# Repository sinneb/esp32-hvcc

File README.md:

# ESP32-DevKitC & hvcc

This repo demonstrates a single file solution for running [hvcc](https://github.com/enzienaudio/hvcc) sources on the [ESP32-devkitc](https://docs.espressif.com/projects/esp-idf/en/latest/hw-reference/get-started-devkitc.html), inspired by the [Faust ESP32 architecture example](https://faust.grame.fr/doc/tutorials/#dsp-on-the-esp32-with-faust). The hvcc compiler leverages the use of (a subset of) puredata operators on the cheap and fast esp32 uprocessor. The ESP32-devkitc combined with one PCM5102 CODEC, one WM8731 CODEC and an 8 port MCP3208 ADC provides a complete and available audio development platform with a very reasonable pricetag. UI provided via 4 buttons, 4 potentiometers and 4 leds.

# Goal

The goal of this development is to realise a generic eurorack module that is based on the ESP32 and programmable via puredata. Each cheap module consists of four control voltage inputs and four audio / cv outputs (all io -5v -> +5v and fully eurorack compatible). All parts are easily obtainable and all software and hardware is open source, so ordering your own set of PCB's is also possible

# Status
15-nov-2020: Replaced one of the PCM5102 with a WM8731 to have audio stereo line in over i2s

25-oct-2020: PCB design ready, gerbers generated and boards ordered.

18-oct-2020: Code cleanup and PCB design ongoing. Current schematic tested and working!

# Installation

- Install Espressif IoT Development Framework 4.1, the official development framework for ESP32.
- Install the hvcc compiler
- Clone this repo

# Hardware setup

Check the Kicad schematics in the schematics folder

# Usage

- Create your puredata patch, using the [supported objects](supportedobjects.md) only. Use `tabread` with a $0-array instead of the `table` object, seems to work better.
- Issue a Issue a `python2.7 hvcc.py input.pd -o ./heavy/` to generate the source files, where input.pd is your puredata patch
- MAC: compile using hvcc and libs and copy to project subdir: `python2.7 hvcc.py esp32_2.pd -p ./Hoclib/ ./Josephlarralde/ ./ParkinsonHashizume/ ./MikeMorenoAudio/ ./Heavylib -o ./heavy/ ; cp ./heavy/c/Heavy_heavy.* ~/Documents/GitHub/esp32-hvcc/main/heavy/`
- WIN: compile and copy: `c:\Python27\python.exe` rest as above, then a `copy /Y heavy\c\Heavy_* c:\Users\Arthur\Github\esp32-hvcc\main\heavy`
- Add all heavy c and cpp sources to /main/CMakeLists.txt (only when adding new objects)
- Run `idf.py -p /dev/tty.SLAB_USBtoUART flash monitor` to compile, upload and monitor the esp32 binary
- MAC: `idf.py -p /dev/cu.usbserial-1A14301 -b 921600 flash monitor`
- WIN: `idf.py -p COM4 -b 921600 flash monitor`
- Enjoy your pd patch!

# Performance

A large and nice sounding puredata patch from "manwithfeathers" on rebeltech.org named ["Fascination IV"](https://www.rebeltech.org/patch-library/patch/Fascination_IV) yields about 60% performance of the ESP32 which looks like a very nice performance / cost ratio!

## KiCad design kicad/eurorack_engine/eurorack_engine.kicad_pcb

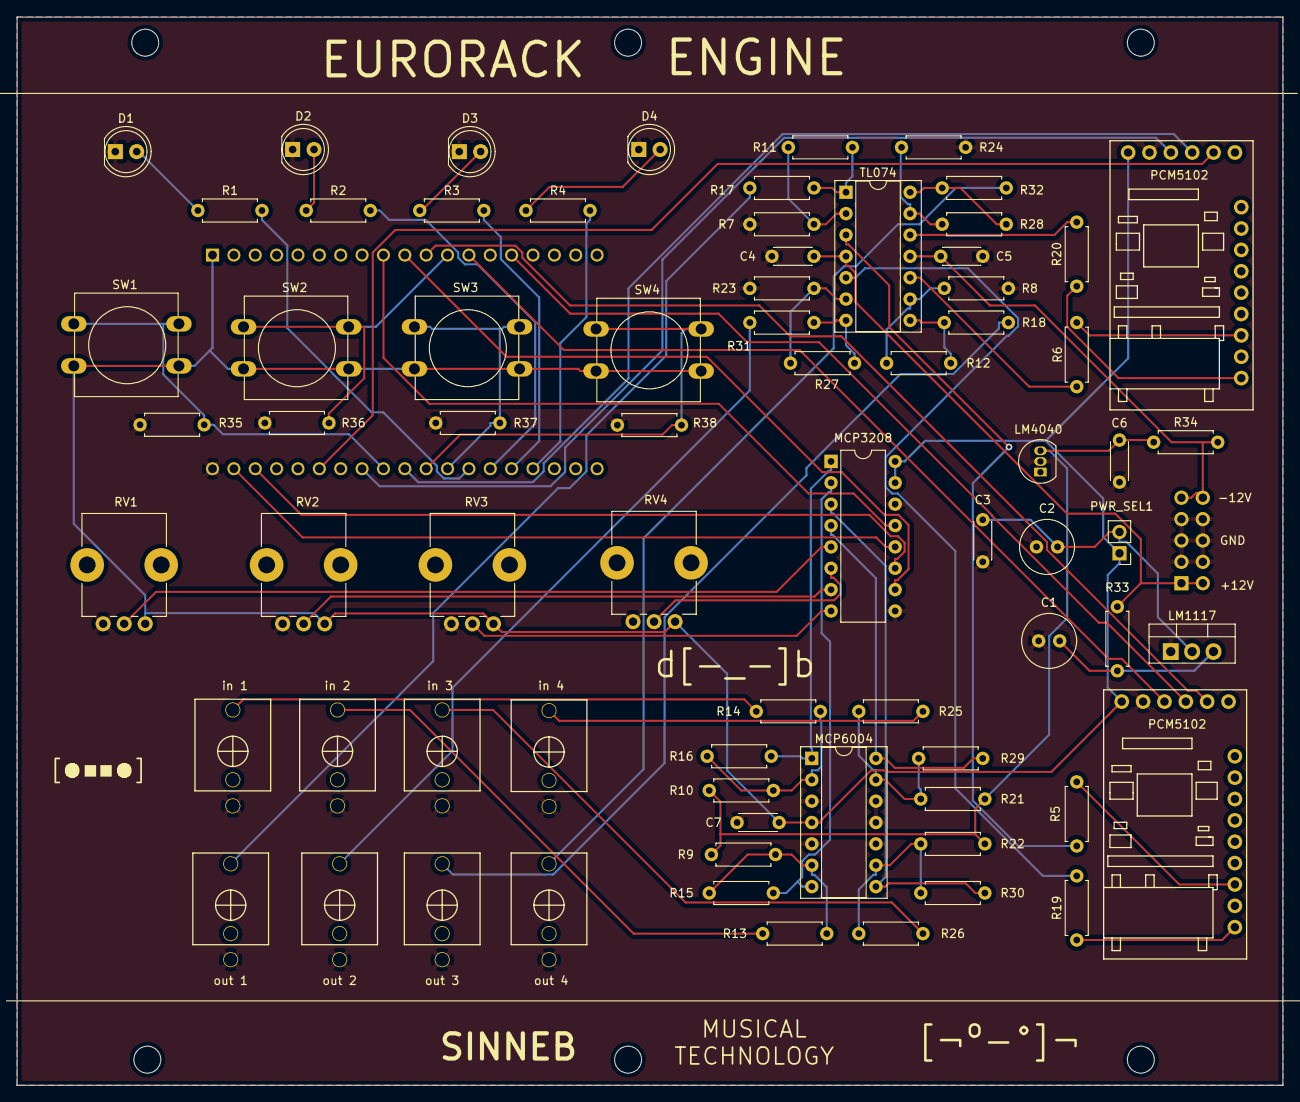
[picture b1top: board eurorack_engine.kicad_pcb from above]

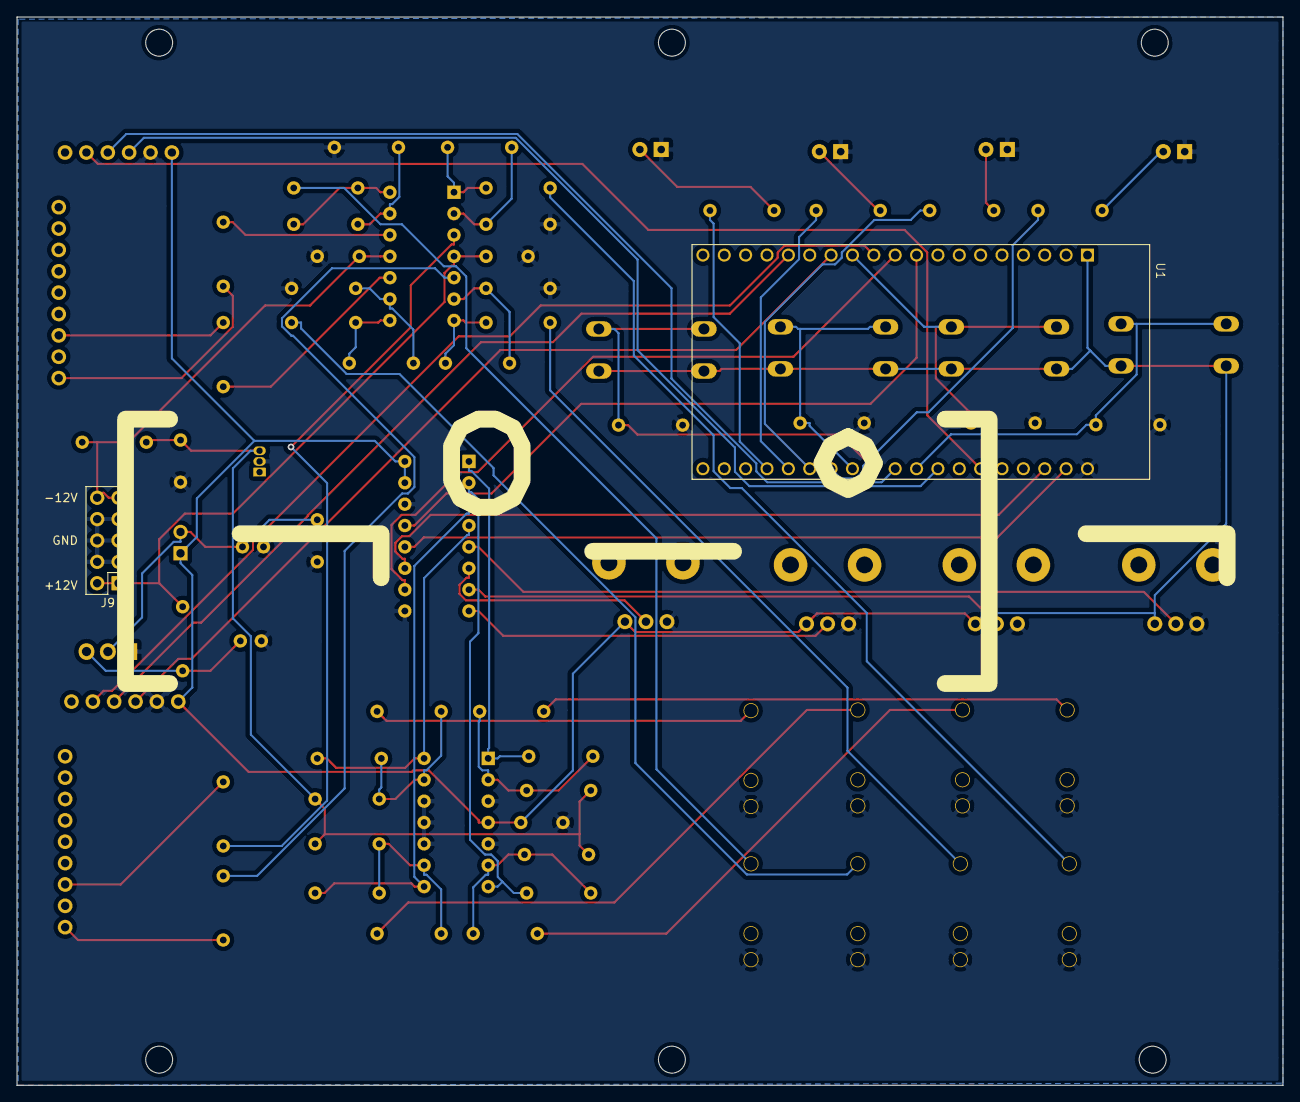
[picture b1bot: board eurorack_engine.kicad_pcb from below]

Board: 2 copper layers, 150.5 x 127.0 mm, 81 parts (2 on the bottom side), 65 nets.

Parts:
C1, C2: 47uf; C_Radial_D6.3mm_H5.0mm_P2.50mm
C3, C4, C5, C6, C7: 100n; C_Disc_D4.3mm_W1.9mm_P5.00mm
D1, D2, D3, D4: LED; LED_D5.0mm
H1, H2, H3, H4, H5, H6: MountingHole; MountingHole_3.2mm_M3
J9: EURO_PWR_2x5; PinHeader_2x05_P2.54mm_Vertical
LM1117: LM1117-3.3; TO-220-3_Vertical
LM4040: LM4040LP-10; TO-92_Inline
MCP3208: MCP3208; DIP-16_W7.62mm
MCP6004: MCP6004; DIP-14_W7.62mm_Socket
PCM5102, PCM5102#2: PCM5102
PWR_SEL1: Conn_01x02; PinHeader_1x02_P2.54mm_Vertical
R1, R2, R3, R4: 220r; R_Axial_DIN0207_L6.3mm_D2.5mm_P7.62mm_Horizontal
R5, R6, R17, R18, R19, R20, R31, R32: 1k; R_Axial_DIN0207_L6.3mm_D2.5mm_P7.62mm_Horizontal
R7, R8, R11, R12, R23, R24, R27, R28, R35, R36, R37, R38: 10k; R_Axial_DIN0207_L6.3mm_D2.5mm_P7.62mm_Horizontal
R9, R10, R21, R22: 200k; R_Axial_DIN0207_L6.3mm_D2.5mm_P7.62mm_Horizontal
R13, R14, R25, R26: 100k; R_Axial_DIN0207_L6.3mm_D2.5mm_P7.62mm_Horizontal
R15, R16, R29, R30: 33k; R_Axial_DIN0207_L6.3mm_D2.5mm_P7.62mm_Horizontal
R33: 4r7; R_Axial_DIN0207_L6.3mm_D2.5mm_P7.62mm_Horizontal
R34: 2k2; R_Axial_DIN0207_L6.3mm_D2.5mm_P7.62mm_Horizontal
RV1, RV2, RV3, RV4: R_POT; Potentiometer_Alps_RK09K_Single_Vertical
SW1, SW2, SW3, SW4: SW_Push; SW_PUSH-12mm
TL074: TL074; DIP-14_W7.62mm_Socket
U1: ESP32-DEVKITC-32D; MODULE_ESP32-DEVKITC-32D
in 1: cv in 1; PJ301M-12
in 2: cv in 2; PJ301M-12
in 3: cv in 3; PJ301M-12
in 4: cv in 4; PJ301M-12
out 1: codec out 1; PJ301M-12
out 2: codec out 2; PJ301M-12
out 3: codec out 3; PJ301M-12
out 4: codec out 4; PJ301M-12

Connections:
+3V3: C7.2, MCP3208.15, MCP3208.16, MCP6004.4, PCM5102.1, PCM5102#2.1, PWR_SEL1.1, RV1.1, RV2.1, RV3.1, RV4.1, SW1.2, SW2.2, SW3.2, SW4.2, U1.1
+12V: C4.2, J9.1, J9.2, R33.1, TL074.4
-12V: C5.1, J9.9, J9.10, R34.2, TL074.11
/adc_ch0: MCP3208.1, MCP6004.1, R16.2
/adc_ch1: MCP3208.2, MCP6004.7, R15.2
/adc_ch2: MCP3208.3, MCP6004.8, R30.2
/adc_ch3: MCP3208.4, MCP6004.14, R29.2
/adc_ch4: MCP3208.5, RV1.2
/adc_ch5: MCP3208.6, RV4.2
/adc_ch6: MCP3208.7, RV2.2
/adc_ch7: MCP3208.8, RV3.2
/adc_clk: MCP3208.13, U1.9
/adc_cs: MCP3208.10, U1.10
/adc_miso: MCP3208.12, U1.21
/adc_mosi: MCP3208.11, U1.22
/aref_-10v: C6.1, LM4040.3, R9.1, R10.1, R21.1, R22.1, R34.1
/bck1: PCM5102#2.5, U1.11
/bck2: PCM5102.5, U1.25
/button1: R36.2, SW2.1, U1.12
/button2: R37.2, SW3.1, U1.31
/button3: R38.2, SW4.1, U1.30
/button4: R35.2, SW1.1, U1.28
/codec_out_1: PCM5102#2.13, R5.1
/codec_out_2: PCM5102#2.15, R19.1
/codec_out_3: PCM5102.13, R6.1
/codec_out_4: PCM5102.15, R20.1
/din1: PCM5102#2.4, U1.15
/din2: PCM5102.4, U1.29
/led1: R1.2, U1.32
/led2: R2.2, U1.33
/led3: R3.2, U1.34
/led4: R4.2, U1.35
/lrck1: PCM5102#2.3, U1.13
/lrck2: PCM5102.3, U1.27
GND: C1.2, C2.2, C3.1, C4.1, C5.2, C6.2, C7.1, D1.1, D2.1, D3.1, D4.1, J9.3, J9.4, J9.5, J9.6, J9.7, J9.8, LM1117.1, LM4040.2, MCP3208.9, MCP3208.14, MCP6004.3, MCP6004.5, MCP6004.10, MCP6004.11, MCP6004.12, PCM5102.2, PCM5102#2.2, R7.2, R8.2, R23.2, R24.2, R35.1, R36.1, R37.1, R38.1, RV1.3, RV2.3, RV3.3, RV4.3, U1.20, in 1.1, in 2.1, in 3.1, in 4.1, out 1.1, out 2.1, out 3.1, out 4.1
unnamed: C1.1, LM1117.3, R33.2
unnamed: C2.1, C3.2, LM1117.2, PWR_SEL1.2
unnamed: D1.2, R1.1
unnamed: D2.2, R2.1
unnamed: D3.2, R3.1
unnamed: D4.2, R4.1
unnamed: R13.1, in 2.3
unnamed: R14.1, in 1.3
unnamed: R17.2, out 1.3
unnamed: R18.2, out 3.3
unnamed: R25.1, in 4.3
unnamed: R26.1, in 3.3
unnamed: R31.2, out 2.3
unnamed: R32.2, out 4.3
unnamed: R5.2, TL074.3
unnamed: R6.2, TL074.10
unnamed: MCP6004.2, R10.2, R14.2, R16.1
unnamed: R7.1, R11.1, TL074.2
unnamed: R11.2, R17.1, TL074.1
unnamed: R8.1, R12.1, TL074.9
unnamed: R12.2, R18.1, TL074.8
unnamed: MCP6004.6, R9.2, R13.2, R15.1
unnamed: R19.2, TL074.5
unnamed: R20.2, TL074.12
unnamed: MCP6004.13, R21.2, R25.2, R29.1
unnamed: MCP6004.9, R22.2, R26.2, R30.1
unnamed: R23.1, R27.1, TL074.6
unnamed: R24.1, R28.1, TL074.13
unnamed: R27.2, R31.1, TL074.7
unnamed: R28.2, R32.1, TL074.14

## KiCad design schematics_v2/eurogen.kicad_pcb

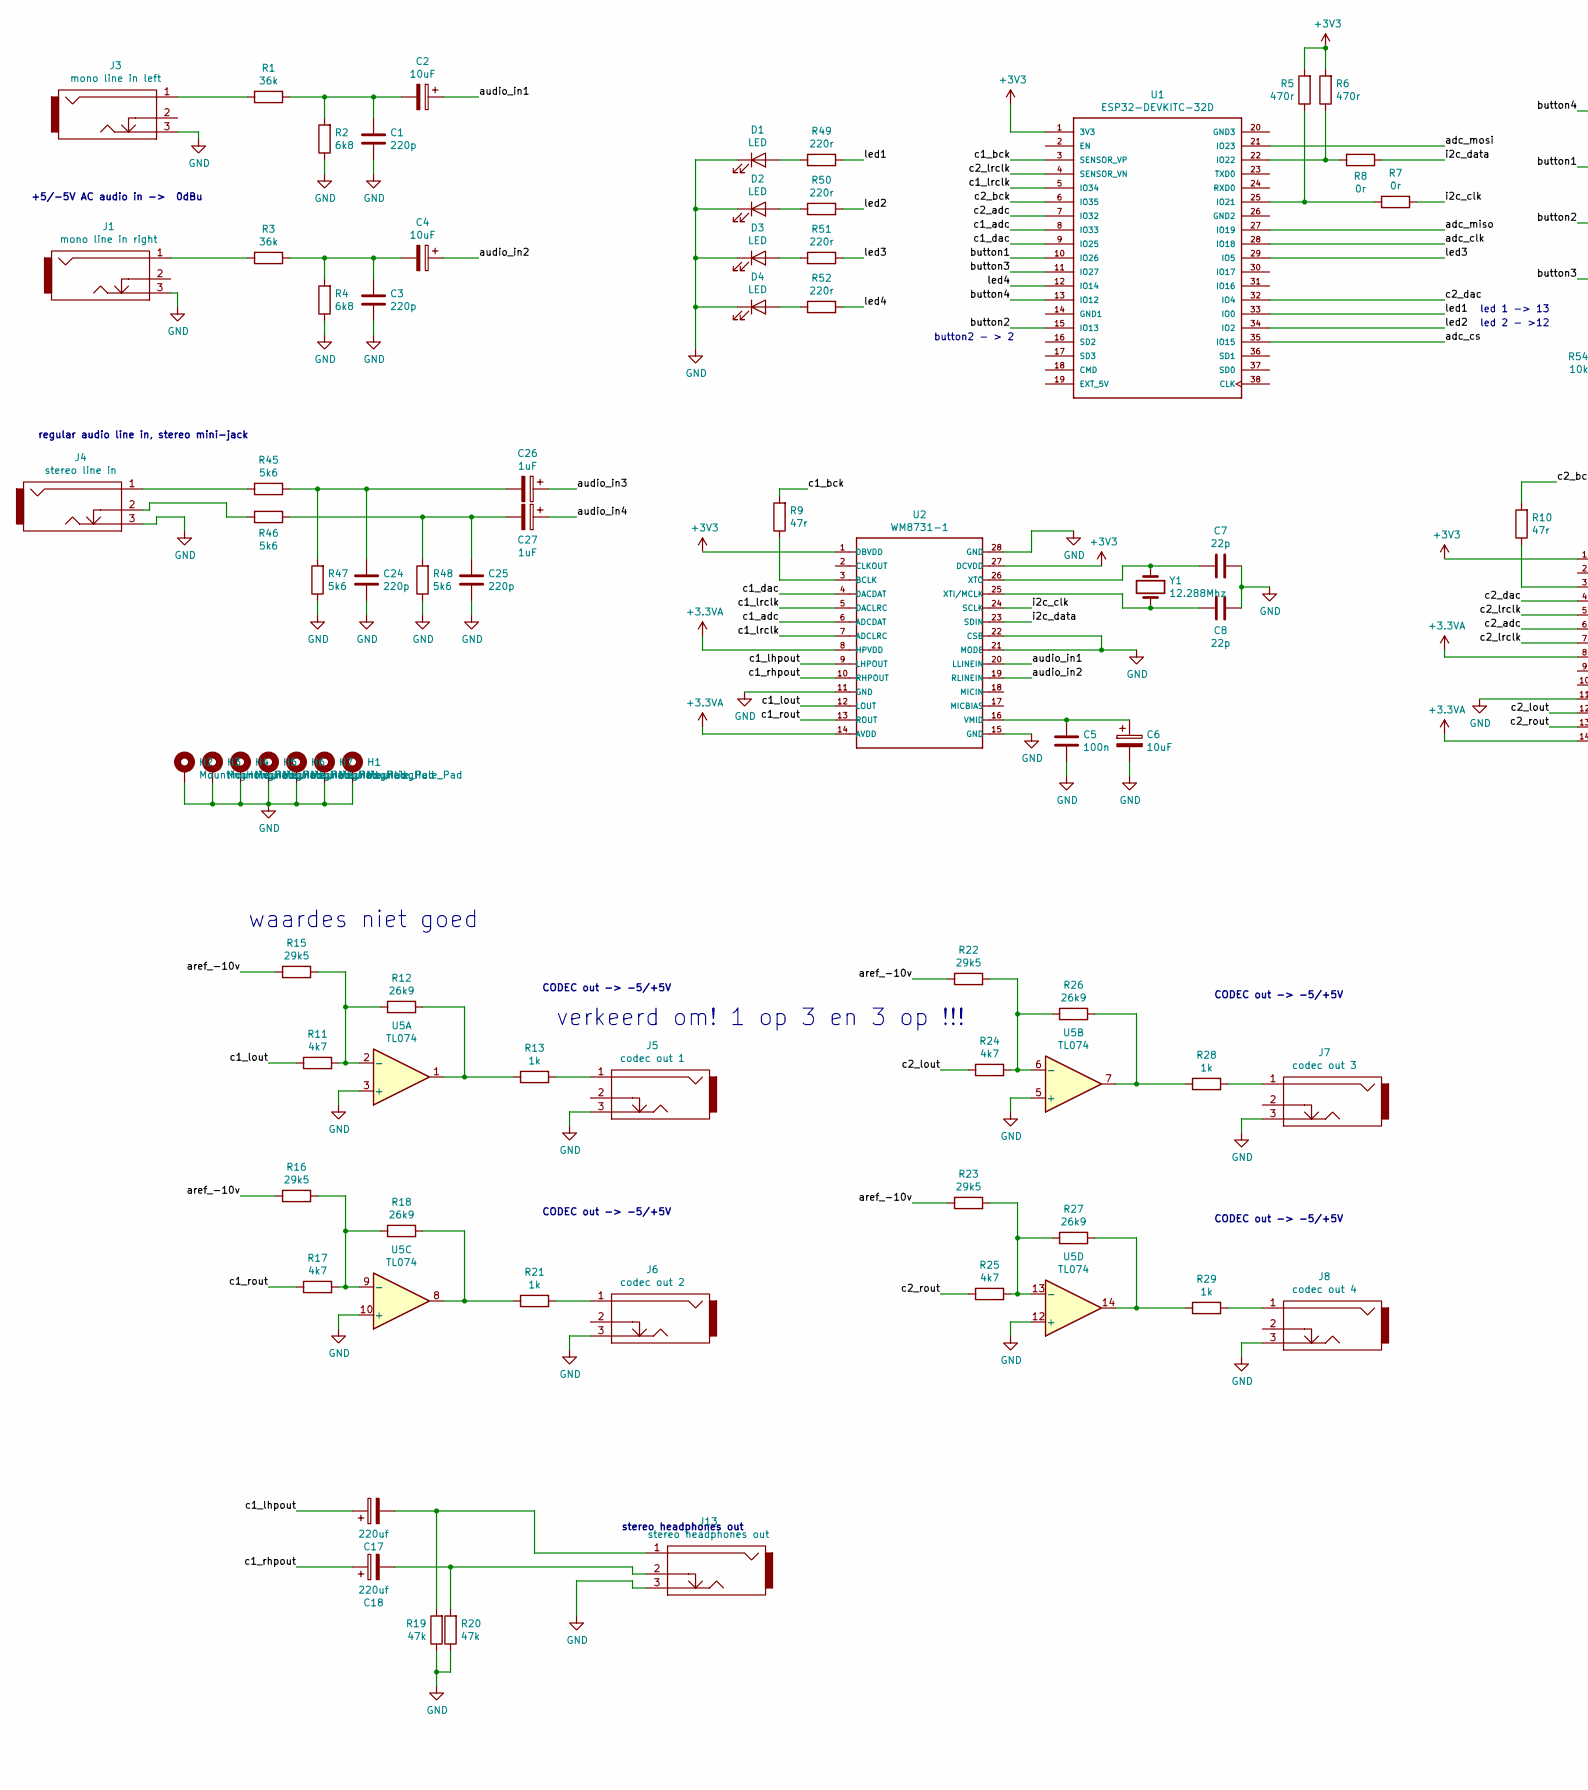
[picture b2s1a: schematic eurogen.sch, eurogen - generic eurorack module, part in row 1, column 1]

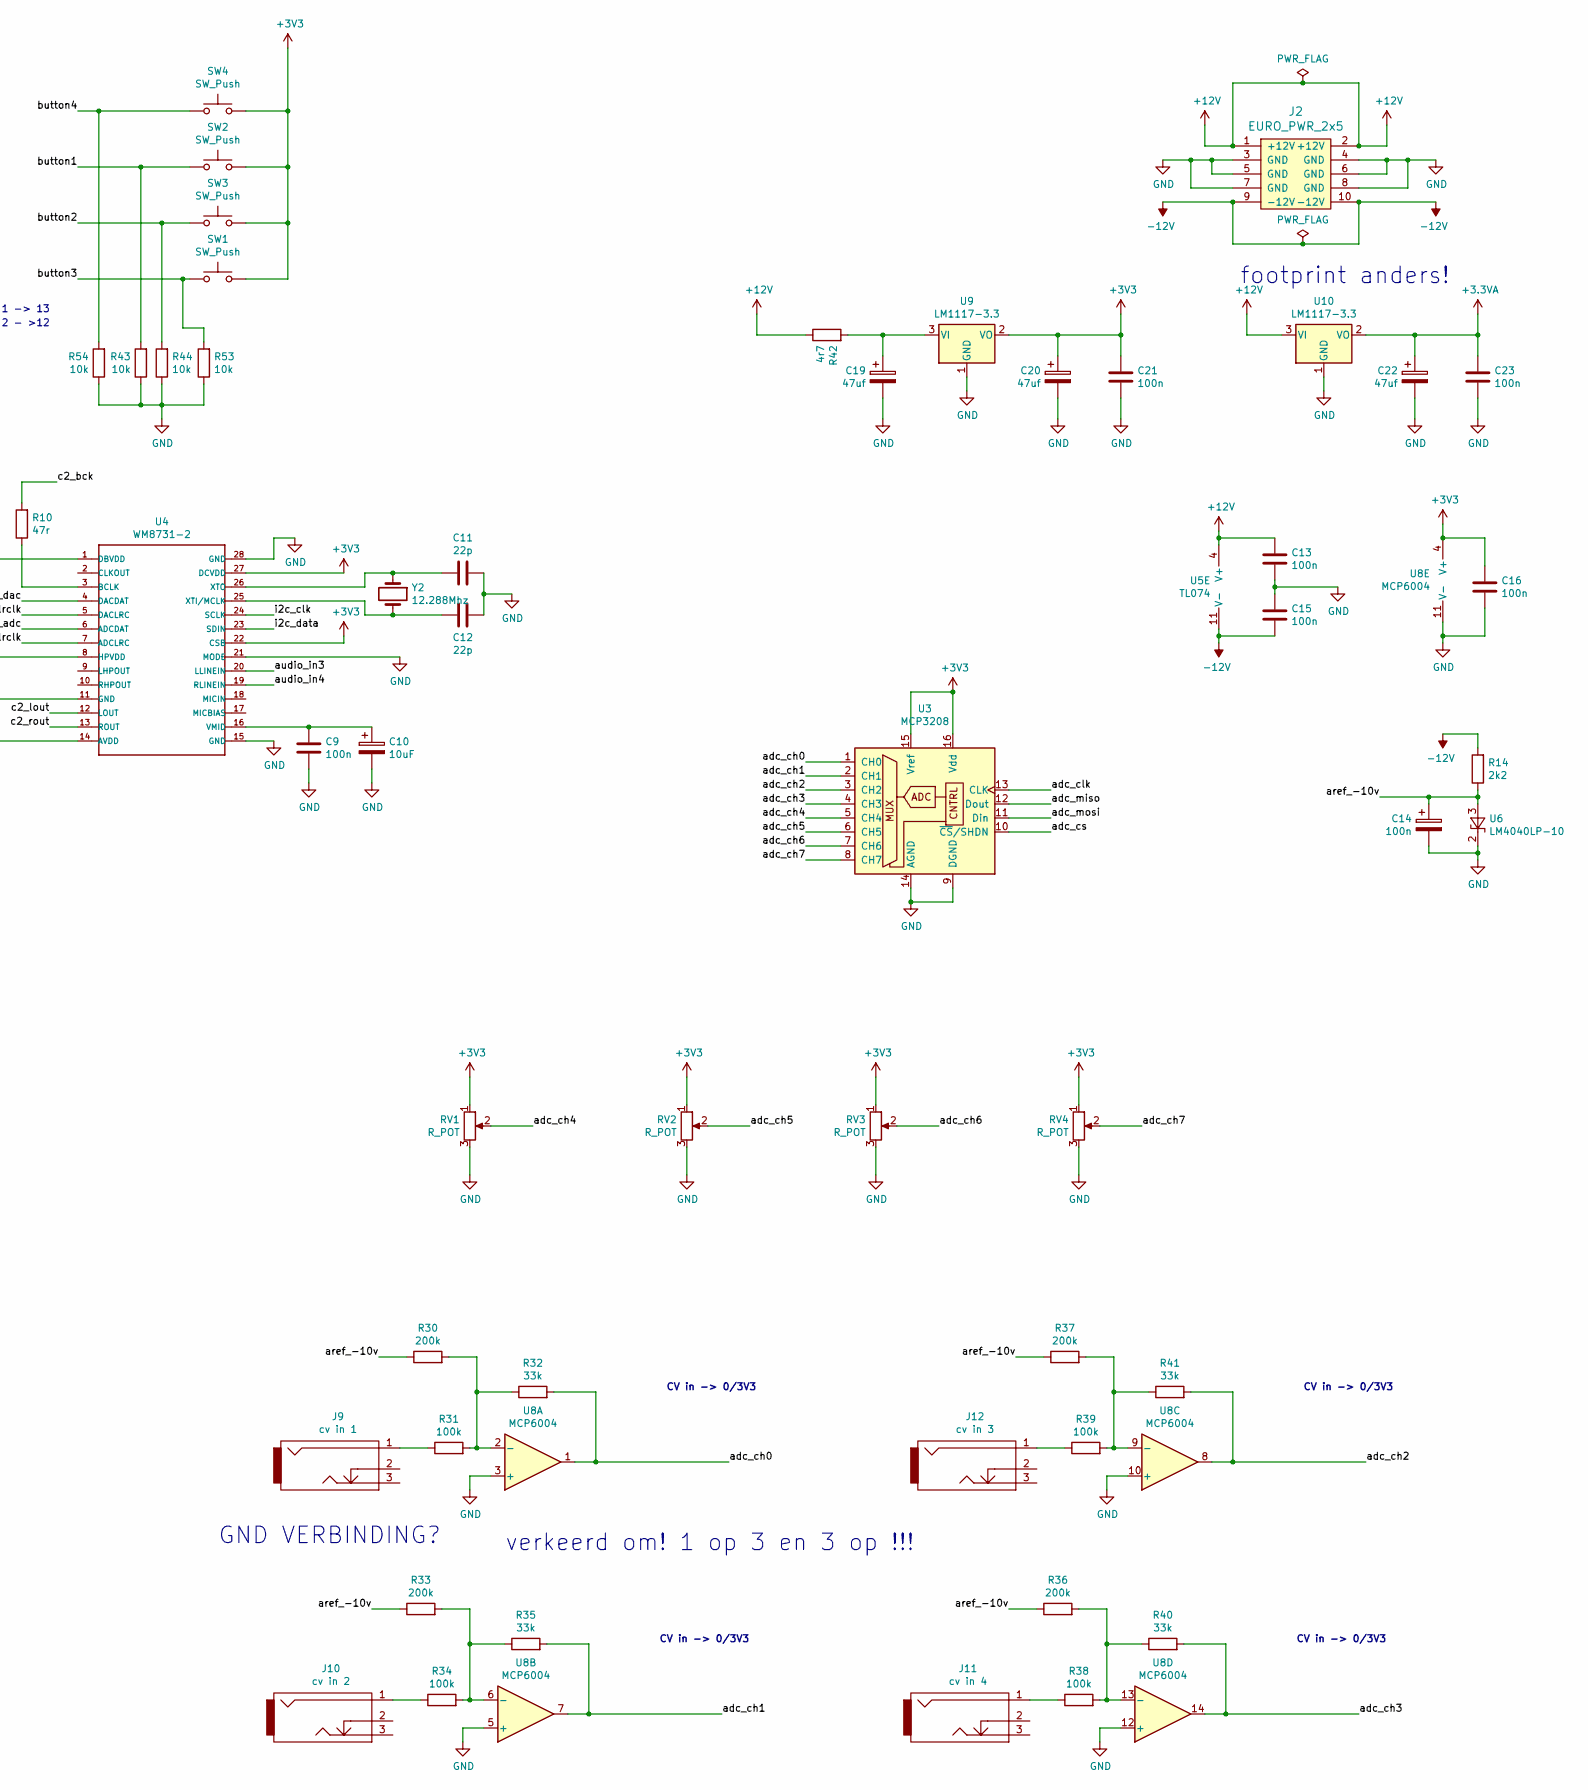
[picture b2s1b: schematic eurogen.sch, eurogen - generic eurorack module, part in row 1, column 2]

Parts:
C1, C3, C24, C25: 220p; C_Disc_D3.0mm_W1.6mm_P2.50mm
C2, C4, C6, C10: 10uF; CP_Radial_D4.0mm_P1.50mm
C5, C9, C13, C14, C15, C16, C21, C23: 100n; C_Disc_D4.3mm_W1.9mm_P5.00mm
C7, C8, C11, C12: 22p; C_Disc_D3.0mm_W1.6mm_P2.50mm
C17, C18: 220uf; C_Radial_D6.3mm_H5.0mm_P2.50mm
C19, C20, C22: 47uf; C_Radial_D6.3mm_H5.0mm_P2.50mm
C26, C27: 1uF; CP_Radial_D4.0mm_P1.50mm
D1, D2, D3, D4: LED; LED_D5.0mm
H1, H2, H3, H4, H5, H6, H7: MountingHole_Pad; MountingHole_3.2mm_M3_Pad
J1: mono line in right; PJ301M-12
J2: EURO_PWR_2x5; PinHeader_2x05_P2.54mm_Vertical
J3: mono line in left; PJ301M-12
J4: stereo line in; PJ301M-12
J5: codec out 1; PJ301M-12
J6: codec out 2; PJ301M-12
J7: codec out 3; PJ301M-12
J8: codec out 4; PJ301M-12
J9: cv in 1; PJ301M-12
J10: cv in 2; PJ301M-12
J11: cv in 4; PJ301M-12
J12: cv in 3; PJ301M-12
J13: stereo headphones out; PJ301M-12
R1, R3: 36k; R_Axial_DIN0207_L6.3mm_D2.5mm_P7.62mm_Horizontal
R2, R4: 6k8; R_Axial_DIN0207_L6.3mm_D2.5mm_P7.62mm_Horizontal
R5, R6: 470r; R_Axial_DIN0207_L6.3mm_D2.5mm_P7.62mm_Horizontal
R7, R8: 0r; R_Axial_DIN0207_L6.3mm_D2.5mm_P7.62mm_Horizontal
R9, R10: 47r; R_Axial_DIN0207_L6.3mm_D2.5mm_P7.62mm_Horizontal
R11, R17, R24, R25: 4k7; R_Axial_DIN0207_L6.3mm_D2.5mm_P7.62mm_Horizontal
R12, R18, R26, R27: 26k9; R_Axial_DIN0207_L6.3mm_D2.5mm_P7.62mm_Horizontal
R13, R21, R28, R29: 1k; R_Axial_DIN0207_L6.3mm_D2.5mm_P7.62mm_Horizontal
R14: 2k2; R_Axial_DIN0207_L6.3mm_D2.5mm_P7.62mm_Horizontal
R15, R16, R22, R23: 29k5; R_Axial_DIN0207_L6.3mm_D2.5mm_P7.62mm_Horizontal
R19, R20: 47k; R_Axial_DIN0207_L6.3mm_D2.5mm_P7.62mm_Horizontal
R30, R33, R36, R37: 200k; R_Axial_DIN0207_L6.3mm_D2.5mm_P7.62mm_Horizontal
R31, R34, R38, R39: 100k; R_Axial_DIN0207_L6.3mm_D2.5mm_P7.62mm_Horizontal
R32, R35, R40, R41: 33k; R_Axial_DIN0207_L6.3mm_D2.5mm_P7.62mm_Horizontal
R42: 4r7; R_Axial_DIN0207_L6.3mm_D2.5mm_P7.62mm_Horizontal
R43, R44, R53, R54: 10k; R_Axial_DIN0207_L6.3mm_D2.5mm_P7.62mm_Horizontal
R45, R46, R47, R48: 5k6; R_Axial_DIN0207_L6.3mm_D2.5mm_P7.62mm_Horizontal
R49, R50, R51, R52: 220r; R_Axial_DIN0207_L6.3mm_D2.5mm_P7.62mm_Horizontal
RV1, RV2, RV3, RV4: R_POT; Potentiometer_Alps_RK09K_Single_Vertical
SW1, SW2, SW3, SW4: SW_Push; SW_PUSH-12mm
U1: ESP32-DEVKITC-32D; MODULE_ESP32-DEVKITC-32D
U2: WM8731-1; SSOP28-0.65-10.2X5.2MM
U3: MCP3208; DIP-16_W7.62mm_Socket
U4: WM8731-2; SSOP28-0.65-10.2X5.2MM
U5: TL074; DIP-14_W7.62mm_Socket
U6: LM4040LP-10; TO-92_Inline
U8: MCP6004; DIP-14_W7.62mm_Socket
U9, U10: LM1117-3.3; TO-92
Y1, Y2: 12.288Mhz; XTAL_ECS-160-20-4X

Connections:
+3.3VA: C22.1, C23.2, U2.8 (HPVDD), U2.14 (AVDD), U4.8 (HPVDD), U4.14 (AVDD), U10.2 (VO)
+12V: C13.2, J2.1 (+12V), J2.2 (+12V), R42.1, U5.4 (V+), U10.3 (VI)
-12V: C15.1, J2.9 (-12V), J2.10 (-12V), R14.2, U5.11 (V-)
/adc_ch0: R32.2, U3.1 (CH0), U8.1
/adc_ch1: R35.2, U3.2 (CH1), U8.7
/adc_ch2: R41.2, U3.3 (CH2), U8.8
/adc_ch3: R40.2, U3.4 (CH3), U8.14
/adc_ch4: RV1.2, U3.5 (CH4)
/adc_ch5: RV2.2, U3.6 (CH5)
/adc_ch6: RV3.2, U3.7 (CH6)
/adc_ch7: RV4.2, U3.8 (CH7)
/adc_clk: U1.28 (IO18), U3.13 (CLK)
/adc_cs: U1.35 (IO15), U3.10 (~CS~/SHDN)
/adc_miso: U1.27 (IO19), U3.12 (Dout)
/adc_mosi: U1.21 (IO23), U3.11 (Din)
/aref_-10v: C14.1, R14.1, R15.1, R16.1, R22.1, R23.1, R30.1, R33.1, R36.1, R37.1, U6.3 (A)
/audio_in1: C2.1, U2.20 (LLINEIN)
/audio_in2: C4.1, U2.19 (RLINEIN)
/audio_in3: C26.1, U4.20 (LLINEIN)
/audio_in4: C27.1, U4.19 (RLINEIN)
/button1: R43.2, SW2.1, U1.10 (IO26)
/button2: R44.2, SW3.1, U1.15 (IO13)
/button3: R53.2, SW1.1, U1.11 (IO27)
/button4: R54.2, SW4.1, U1.13 (IO12)
/c1_adc: U1.8 (IO33), U2.6 (ADCDAT)
/c1_bck: R9.2, U1.3 (SENSOR_VP)
/c1_dac: U1.9 (IO25), U2.4 (DACDAT)
/c1_lhpout: C17.1, U2.9 (LHPOUT)
/c1_lout: R11.1, U2.12 (LOUT)
/c1_lrclk: U1.5 (IO34), U2.5 (DACLRC), U2.7 (ADCLRC)
/c1_rhpout: C18.1, U2.10 (RHPOUT)
/c1_rout: R17.1, U2.13 (ROUT)
/c2_adc: U1.7 (IO32), U4.6 (ADCDAT)
/c2_bck: R10.2, U1.6 (IO35)
/c2_dac: U1.32 (IO4), U4.4 (DACDAT)
/c2_lout: R24.1, U4.12 (LOUT)
/c2_lrclk: U1.4 (SENSOR_VN), U4.5 (DACLRC), U4.7 (ADCLRC)
/c2_rout: R25.1, U4.13 (ROUT)
/i2c_clk: R7.1, U2.24 (SCLK), U4.24 (SCLK)
/i2c_data: R8.1, U2.23 (SDIN), U4.23 (SDIN)
/led1: R49.2, U1.33 (IO0)
/led2: R50.2, U1.34 (IO2)
/led3: R51.2, U1.29 (IO5)
/led4: R52.2, U1.12 (IO14)
unnamed: C1.1, C2.2, R1.1, R2.2
unnamed: C3.1, C4.2, R3.1, R4.2
unnamed: C5.1, C6.1, U2.16 (VMID)
unnamed: C7.2, U2.26 (XTO), Y1.1
unnamed: C8.2, U2.25 (XTI/MCLK), Y1.2
unnamed: C9.1, C10.1, U4.16 (VMID)
unnamed: C11.2, U4.26 (XTO), Y2.1
unnamed: C12.2, U4.25 (XTI/MCLK), Y2.2
unnamed: C17.2, J13.1, R19.2
unnamed: C18.2, J13.2, R20.2
unnamed: C19.1, R42.2, U9.3 (VI)
unnamed: C24.1, C26.2, R45.1, R47.2
unnamed: C25.1, C27.2, R46.1, R48.2
unnamed: D1.2 (A), R49.1
unnamed: D2.2 (A), R50.1
unnamed: D3.2 (A), R51.1
unnamed: D4.2 (A), R52.1
unnamed: J1.1, R3.2
unnamed: J3.1, R1.2
unnamed: J4.1, R45.2
unnamed: J4.2, R46.2
unnamed: J5.1, R13.2
unnamed: J6.1, R21.2
unnamed: J7.1, R28.2
unnamed: J8.1, R29.2
unnamed: J9.1, R31.1
unnamed: J10.1, R34.1
unnamed: J11.1, R38.1
unnamed: J12.1, R39.1
unnamed: R5.1, R7.2, U1.25 (IO21)
unnamed: R6.1, R8.2, U1.22 (IO22)
unnamed: R9.1, U2.3 (BCLK)
unnamed: R10.1, U4.3 (BCLK)
unnamed: R11.2, R12.1, R15.2, U5.2 (-)
unnamed: R12.2, R13.1, U5.1
unnamed: R16.2, R17.2, R18.1, U5.9 (-)
unnamed: R18.2, R21.1, U5.8
unnamed: R22.2, R24.2, R26.1, U5.6 (-)
unnamed: R23.2, R25.2, R27.1, U5.13 (-)
unnamed: R26.2, R28.1, U5.7
unnamed: R27.2, R29.1, U5.14
unnamed: R30.2, R31.2, R32.1, U8.2 (-)
unnamed: R33.2, R34.2, R35.1, U8.6 (-)
unnamed: R36.2, R38.2, R40.1, U8.13 (-)
unnamed: R37.2, R39.2, R41.1, U8.9 (-)

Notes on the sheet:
CODEC out -> -5/+5V
stereo headphones out
CV in -> 0/3V3
+5/-5V AC audio in -> 0dBu
regular audio line in, stereo mini-jack
verkeerd om! 1 op 3 en 3 op !!!
waardes niet goed
footprint anders!
led 1 -> 13
led 2 - >12
button2 - > 2
GND VERBINDING?

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
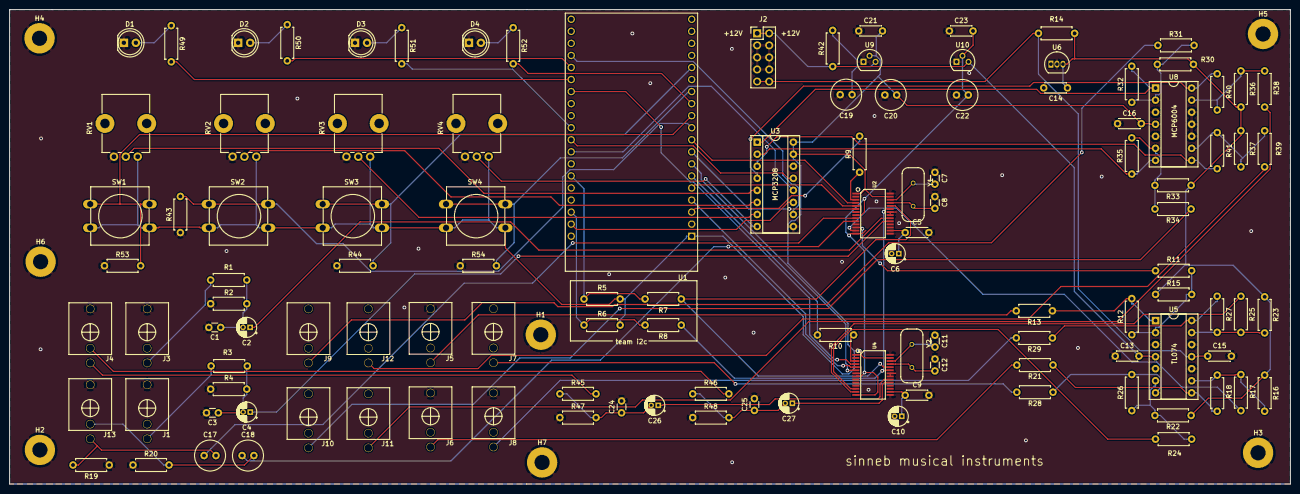
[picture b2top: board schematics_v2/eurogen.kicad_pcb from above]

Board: 2 copper layers, 270.0 x 100.0 mm, 124 parts (0 on the bottom side), 91 nets.

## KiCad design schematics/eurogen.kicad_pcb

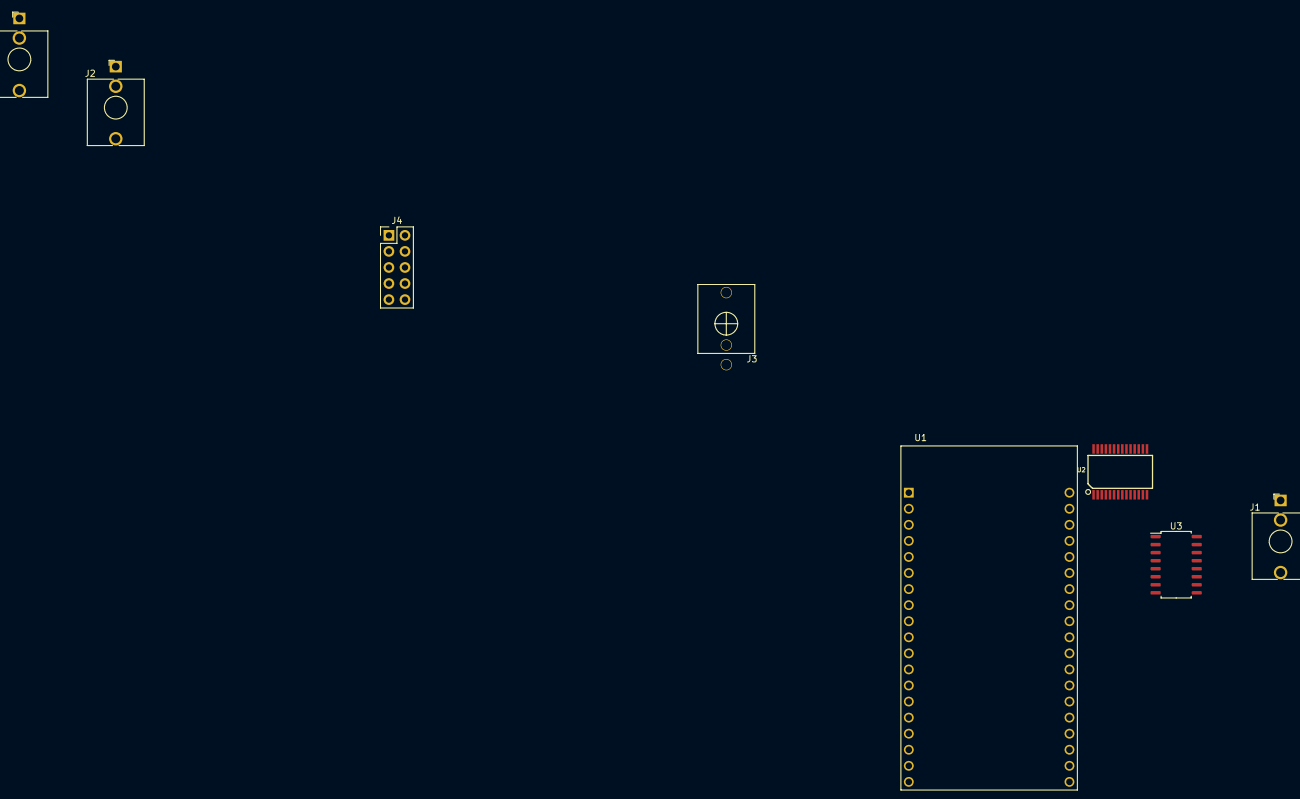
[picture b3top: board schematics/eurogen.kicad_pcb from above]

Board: 2 copper layers, 8 parts (0 on the bottom side), 3 nets, no tracks yet.

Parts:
J1: AudioJack2; Jack_3.5mm_QingPu_WQP-PJ398SM_Vertical_CircularHoles
J2: AudioJack2_Ground_SwitchT; Jack_3.5mm_QingPu_WQP-PJ398SM_Vertical_CircularHoles
J2#2: AudioJack2_SwitchT; Jack_3.5mm_QingPu_WQP-PJ398SM_Vertical_CircularHoles
J3: PJ301M-12
J4: EURO_PWR_2x5; PinHeader_2x05_P2.54mm_Vertical
U1: ESP32-DEVKITC-32D; MODULE_ESP32-DEVKITC-32D
U2: CODECODER-WM8731SEDS_V(SSOP28); SSOP28-0.65-10.2X5.2MM
U3: MCP3208; SOIC-16_4.55x10.3mm_P1.27mm

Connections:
unnamed: J2.S, J2#2.S
unnamed: J2.T, J2#2.T
unnamed: J2.TN, J2#2.TN

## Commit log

2020-02-08 initial upload
2020-02-08 Update README.md
    working on the readme
2020-02-09 Updated readme and added supported objects
2020-02-09 Revert "Updated readme and added supported objects"
    This reverts commit 8526afb6982fdc61779a1610d438353b4a00fbd3.
2020-02-09 Revert "Revert "Updated readme and added supported objects""
    This reverts commit b1cce1c03a0bb2306ae963d2211054a56cb747da.
2020-02-10 updated memory settings in sdkconfig
2020-02-11 Added u8g2 drivers for SSD1306 OLED display
2020-02-17 added rotary encoder support
2020-02-19 wm8731 working! next up: code clean issues
2020-02-19 Added 12khz ADC read over VSPI & DMA
2020-02-29 small type changes
    + new development machine
2020-02-29 added schematics, fixed oled
2020-03-01 added rotary encoder. schematics PDF
2020-03-06 pin numbers updates, continued work on ADC
2020-03-06 succesful dma buffer experiments
2020-03-07 first dual wm8731 support
2020-03-08 changes to make WM8731 master
    countering:
    problems with reliable i2c
    problems with dual codec
2020-03-08 WM8731 i2c fixed
    changed resistor values
    confirmed schematic
2020-03-14 i2c with auto retry, fixes for double i2s
2020-03-15 experimental changes!
2020-03-20 gpio updates, schematics update
2020-03-22 schematic updates
2020-03-27 before cleanup
2020-03-27 after cleanup
2020-04-12 fixed button in
    now both 26 and 32 work
2020-04-13 pwm led 0, 2 and 5 working
2020-04-17 sendhook implemented
2020-04-30 led fixes and small cleanup
2020-05-07 audio processing to core 1
2020-05-08 fixes and updates
    adc sample rate
    pd patch communication
2020-05-10 wm8731 fixes
2020-05-14 schematics update
2020-10-18 push before rework
2020-10-18 code cleanup
2020-10-19 schematic update
2020-10-21 updated schematics
2020-10-22 schematic final
